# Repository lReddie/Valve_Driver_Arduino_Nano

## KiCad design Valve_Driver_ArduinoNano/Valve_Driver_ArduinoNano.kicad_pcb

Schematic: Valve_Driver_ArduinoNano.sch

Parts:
A1: Arduino_Nano_v3.x; Arduino_Nano
C1, C2, C3, C4, C5, C6, C7, C8, C9, C10, C11, C13, C14, C15, C16, C17, C18, C21, C22, C23, C24, C29, C30, C32: C; C_0603_1608Metric_Pad1.05x0.95mm_HandSolder
C31, C33: C; C_0805_2012Metric_Pad1.15x1.40mm_HandSolder
D1, D2, D3, D4, D5, D6: D_Schottky; D_SOD-123
J1: Barrel_Jack; CUI_PJ-082BH
J2: Conn_01x03_Female; PinHeader_1x03_P2.54mm_Vertical
J3, J4, J5, J6, J8, J9: Conn_01x02; PinHeader_1x02_P2.54mm_Vertical
J7: Conn_01x12; PhoenixContact_MSTBVA_2,5_12-G_1x12_P5.00mm_Vertical
J10: Conn_01x08; PhoenixContact_MSTBV_2,5_8-GF-5,08_1x08_P5.08mm_Vertical_Th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
Q1, Q4, Q7, Q10, Q13, Q17: 2N7002; SOT-23
R1, R2, R3, R4, R5, R6, R7, R8, R9, R10, R11, R13, R15, R16, R17, R19, R20, R31, R34, R38, R40, R42, R44, R45, R46, R50, R58, R60, R65, R67, R68, R69, R70, R77, R79, R80, R81, R82: R; R_0603_1608Metric_Pad1.05x0.95mm_HandSolder
R12, R14, R41, R43, R64, R66: R; R_1206_3216Metric_Pad1.42x1.75mm_HandSolder
SW1, SW2, SW3, SW4, SW5, SW6: SW_Push; SW_SPST_EVQP0
U1: OPA333xxDBV; SOT-23-5
U3, U4, U7, U8, U11, U12: INA186; SOT-23-5_HandSoldering
U14: LM340_SOT223; SOT-223
U15: REF3033; SOT-23

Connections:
+5V: C1.1, C2.1, C3.1, C9.1, C10.1, C17.1, C18.1, C29.1, C32.1, C33.1, R5.2, R6.2, R7.2, R8.2, R10.2, R17.2, U1.5 (V+), U3.3, U4.3, U7.3, U8.3, U11.3, U12.3, U14.3, U15.1 (IN)
+12V: A1.30
/AIR_D_CURR: A1.25, C23.1, R65.1
/AIR_D_Hit: A1.5, R34.2
/AIR_D_On: A1.11, J10.3, R17.1, SW6.1
/AIR_D_RTN: D3.2, J5.2, J7.11, Q7.3 (D)
/AIR_D_VALVE: D3.1, J5.1, J7.12, R58.1, R64.1
/EQ_CURR: A1.21, C8.1, R15.1
/EQ_Hit: A1.9, R70.2
/EQ_On: A1.15, J10.7, R6.1, SW2.1
/EQ_RTN: D5.2, J7.3, J8.2, Q13.3 (D)
/EQ_VALVE: D5.1, J7.4, J8.1, R11.1, R14.1
/FWA_CURR: A1.23, C16.1, R44.1
/FWA_Hit: A1.7, R16.2
/FWA_On: A1.13, J10.5, R8.1, SW4.1
/FWA_RTN: D1.2, J3.2, J7.7, Q1.3 (D)
/FWA_VALVE: D1.1, J3.1, J7.8, R40.1, R43.1
/FWB_CURR: A1.24, C15.1, R42.1
/FWB_Hit: A1.6, R31.2
/FWB_On: A1.12, J10.4, R7.1, SW3.1
/FWB_RTN: D2.2, J4.2, J7.9, Q4.3 (D)
/FWB_VALVE: D2.1, J4.1, J7.10, R38.1, R41.1
/INPUT_POWER: C30.1, C31.1, J1.1, R1.2, R12.2, R14.2, R19.1, R20.1, R41.2, R43.2, R45.1, R46.1, R64.2, R66.2, R68.1, R69.1, U14.1
/OCD_CURR: A1.20, C7.1, R13.1
/OCD_Hit: A1.10, R50.2
/OCD_On: A1.16, J10.8, R5.1, SW1.1
/OCD_RTN: D4.2, J6.2, J7.1, Q10.3 (D)
/OCD_VALVE: D4.1, J6.1, J7.2, R9.1, R12.1
/PUR_CURR: A1.22, C24.1, R67.1
/PUR_Hit: A1.8, R77.2
/PUR_RTN: D6.2, J7.5, J9.2, Q17.3 (D)
/PUR_VALVE: D6.1, J7.6, J9.1, R60.1, R66.1
/Pur_On: A1.14, J10.6, R10.1, SW5.1
/RX: A1.2, J2.1
/TX: A1.1, J2.2
/VALVE_V: A1.19, C4.1, J10.2, R2.2
GND: A1.4, A1.29, C1.2, C2.2, C3.2, C4.2, C7.2, C8.2, C9.2, C10.2, C11.2, C15.2, C16.2, C17.2, C18.2, C23.2, C24.2, C29.2, C30.2, C31.2, C32.2, C33.2, J1.2, J2.3, J10.1, Q1.2 (S), Q4.2 (S), Q7.2 (S), Q10.2 (S), Q13.2 (S), Q17.2 (S), R3.1, SW1.2, SW2.2, SW3.2, SW4.2, SW5.2, SW6.2, U1.2 (V-), U3.1, U4.1, U7.1, U8.1, U11.1, U12.1, U14.2, U14.4, U15.3 (GND)
unnamed: A1.17, R79.1
unnamed: A1.18, R79.2, R80.2, R82.1
unnamed: A1.27, R80.1, R81.1
unnamed: A1.3, A1.28, R81.2
unnamed: C5.1, R9.2, U3.4
unnamed: C5.2, R19.2, U3.5
unnamed: C6.1, R11.2, U4.4
unnamed: C6.2, R20.2, U4.5
unnamed: C11.1, R1.1, R3.2, U1.3 (+)
unnamed: C13.1, R38.2, U7.4
unnamed: C13.2, R45.2, U7.5
unnamed: C14.1, R40.2, U8.4
unnamed: C14.2, R46.2, U8.5
unnamed: C21.1, R58.2, U11.4
unnamed: C21.2, R68.2, U11.5
unnamed: C22.1, R60.2, U12.4
unnamed: C22.2, R69.2, U12.5
unnamed: Q1.1 (G), R16.1
unnamed: Q4.1 (G), R31.1
unnamed: Q7.1 (G), R34.1
unnamed: Q10.1 (G), R50.1
unnamed: Q13.1 (G), R70.1
unnamed: Q17.1 (G), R77.1
unnamed: R2.1, R4.2, U1.1
unnamed: R4.1, U1.4 (-)
unnamed: R13.2, U3.2
unnamed: R15.2, U4.2
unnamed: R42.2, U7.2
unnamed: R44.2, U8.2
unnamed: R65.2, U11.2
unnamed: R67.2, U12.2
unnamed: R82.2, U15.2 (OUT)

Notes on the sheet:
Shield for Arduino Nano

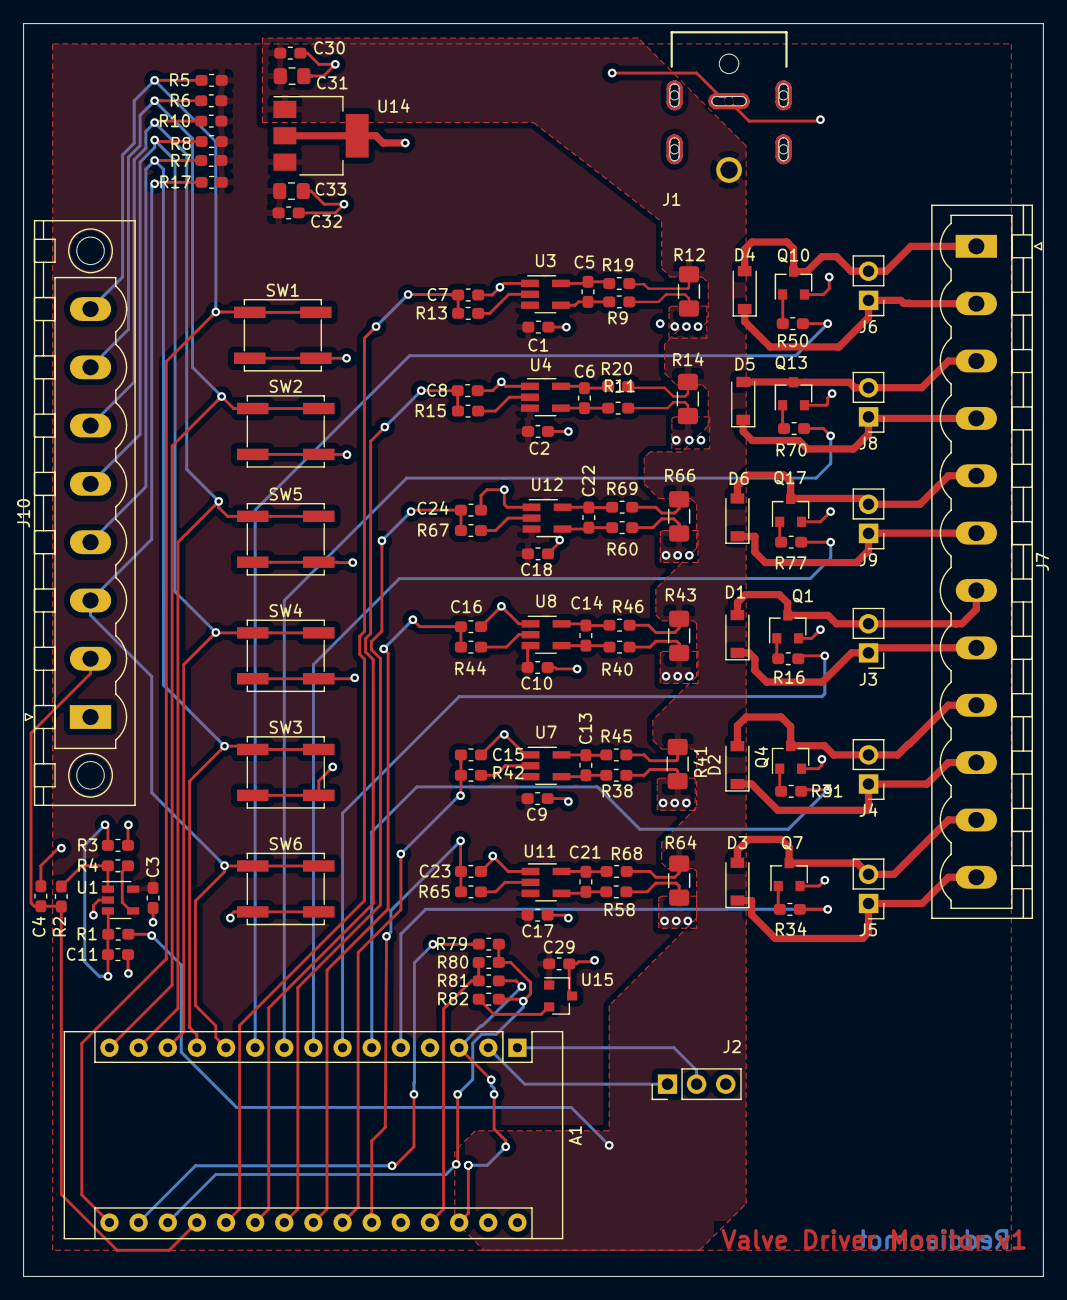
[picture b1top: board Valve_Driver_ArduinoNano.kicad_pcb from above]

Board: 2 copper layers, 88.9 x 109.2 mm, 108 parts (0 on the bottom side), 68 nets.

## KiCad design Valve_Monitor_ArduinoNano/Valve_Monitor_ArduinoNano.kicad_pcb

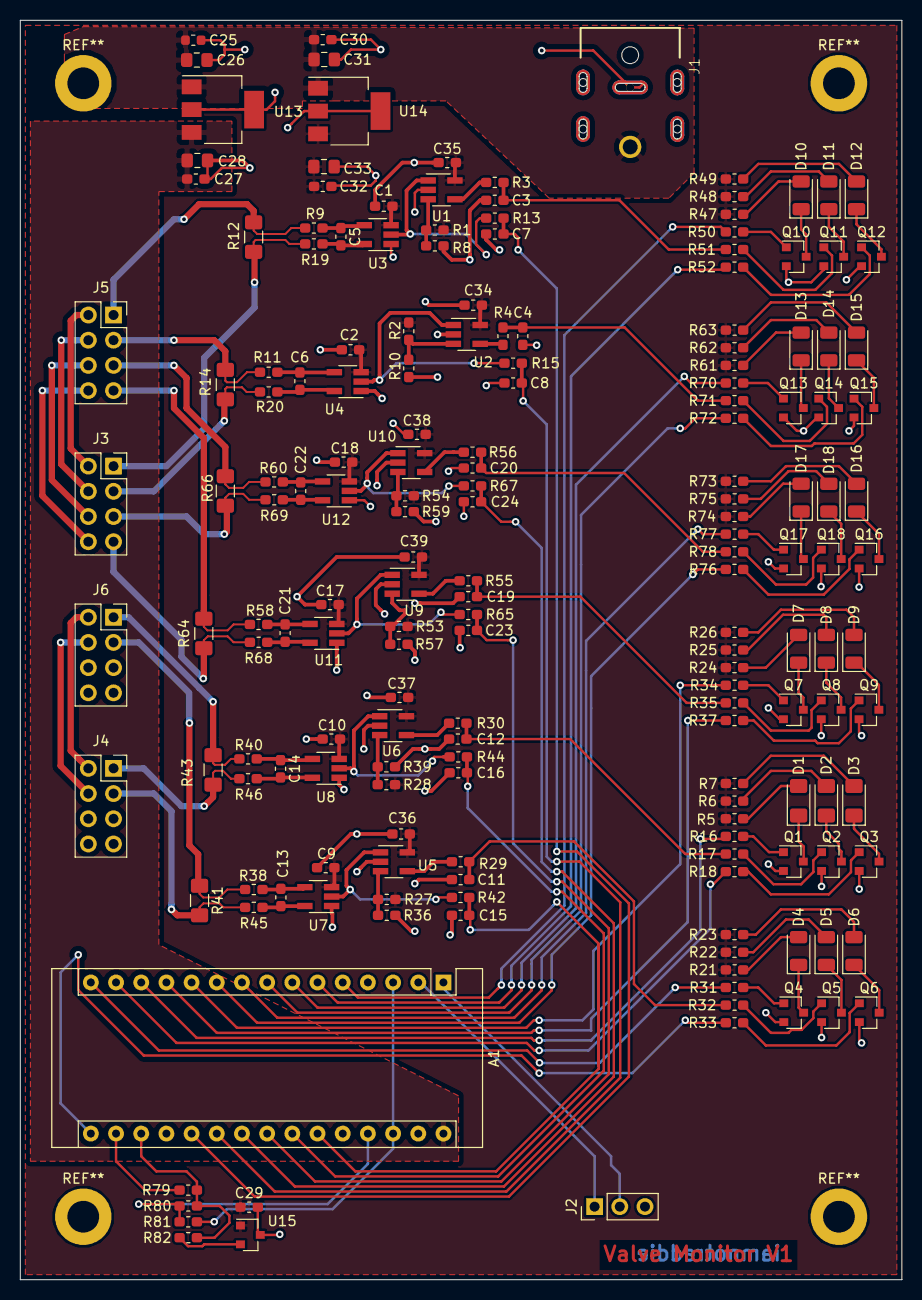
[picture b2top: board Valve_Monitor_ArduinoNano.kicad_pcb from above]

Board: 2 copper layers, 88.9 x 127.0 mm, 179 parts (0 on the bottom side), 137 nets.

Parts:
A1: Arduino_Nano_v3.x; Arduino_Nano
C1, C2, C3, C4, C5, C6, C7, C8, C9, C10, C11, C12, C13, C14, C15, C16, C17, C18, C19, C20, C21, C22, C23, C24, C27, C29, C30, C32, C34, C35, C36, C37, C38, C39: C; C_0603_1608Metric_Pad1.05x0.95mm_HandSolder
C25: C; C_0603_1608Metric
C26, C28, C31, C33: C; C_0805_2012Metric_Pad1.15x1.40mm_HandSolder
D1, D2, D3: LED; LED_1206_3216Metric_Pad1.42x1.75mm_HandSolder
D4, D5, D6, D7, D8, D9, D10, D11, D12, D13, D14, D15, D16, D17, D18: LED; LED_1206_3216Metric
J1: Barrel_Jack; CUI_PJ-082BH
J2: Conn_01x03_Female; PinHeader_1x03_P2.54mm_Vertical
J3, J4, J5, J6: Conn_02x04_Top_Bottom; PinSocket_2x04_P2.54mm_Vertical
Q1, Q2, Q3, Q4, Q5, Q6, Q7, Q8, Q9, Q10, Q11, Q12, Q13, Q14, Q15, Q16, Q17, Q18: 2N7002; SOT-23
R1, R2, R3, R4, R5, R6, R7, R8, R9, R10, R11, R13, R15, R16, R17, R18, R19, R20, R21, R22, R23, R24, R25, R26, R27, R28, R29, R30, R31, R32, R33, R34, R35, R36, R37, R38, R39, R40, R42, R44, R45, R46, R47, R48, R49, R50, R51, R52, R53, R54, R55, R56, R57, R58, R59, R60, R61, R62, R63, R65, R67, R68, R69, R70, R71, R72, R73, R74, R75, R76, R77, R78, R79, R80, R81, R82: R; R_0603_1608Metric_Pad1.05x0.95mm_HandSolder
R12, R14, R41, R43, R64, R66: R; R_1206_3216Metric_Pad1.42x1.75mm_HandSolder
U1, U2, U5, U6, U9, U10: LMV331; SOT-23-5_HandSoldering
U3, U4, U7, U8, U11, U12: INA186; SOT-23-5_HandSoldering
U13, U14: LM340_SOT223; SOT-223
U15: REF3033; SOT-23

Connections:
+5V: C1.1, C2.1, C9.1, C10.1, C17.1, C18.1, C29.1, C32.1, C33.1, C34.1, C35.1, C36.1, C37.1, C38.1, C39.1, R1.1, R2.1, R5.1, R6.1, R7.1, R21.1, R22.1, R23.1, R24.1, R25.1, R26.1, R27.1, R28.1, R47.1, R48.1, R49.1, R53.1, R54.1, R61.1, R62.1, R63.1, R73.1, R74.1, R75.1, U1.5, U2.5, U3.3, U4.3, U5.5, U6.5, U7.3, U8.3, U9.5, U10.5, U11.3, U12.3, U14.3, U15.1
+12V: A1.30, C27.1, C28.1, U13.3
/AIR_D_CURR: A1.23, C23.1, R65.1
/AIR_D_Hit: A1.11, R34.2
/AIR_D_Hold: C19.1, R35.2, R55.1
/AIR_D_PASS: A1.12, R37.2
/AIR_D_PWR: J3.7, R64.2, R68.1
/AIR_D_VALVE: J5.7, R58.1, R64.1
/AIR_D__RTN: J3.8, J5.8
/EQ_CURR: A1.21, C8.1, R15.1
/EQ_Hit: A1.7, R70.2
/EQ_Hold: C4.1, R4.1, R71.2
/EQ_PASS: A1.8, R72.2
/EQ_PWR: J3.3, R14.2, R20.1
/EQ_RTN: J3.4, J5.4
/EQ_VALVE: J5.3, R11.1, R14.1
/FWA_CURR: A1.24, C16.1, R44.1
/FWA_Hit: A1.13, R16.2
/FWA_Hold: C12.1, R17.2, R30.1
/FWA_PASS: A1.14, R18.2
/FWA_PWR: J4.1, R43.2, R46.1
/FWA_RTN: J4.2, J6.2
/FWA_VALVE: J6.1, R40.1, R43.1
/FWB_CURR: A1.25, C15.1, R42.1
/FWB_Hit: A1.15, R31.2
/FWB_Hold: C11.1, R29.1, R32.2
/FWB_PASS: A1.16, R33.2
/FWB_PWR: J4.3, R41.2, R45.1
/FWB_RTN: J4.4, J6.4
/FWB_VALVE: J6.3, R38.1, R41.1
/INPUT_POWER: C25.1, C26.1, C30.1, C31.1, J1.1, U13.1, U14.1
/OCD_CURR: A1.20, C7.1, R13.1
/OCD_Hit: A1.5, R50.2
/OCD_Hold: C3.1, R3.1, R51.2
/OCD_PASS: A1.6, R52.2
/OCD_PWR: J3.1, R12.2, R19.1
/OCD_RTN: J3.2, J5.2
/OCD_VALVE: J5.1, R9.1, R12.1
/PUR_CURR: A1.22, C24.1, R67.1
/PUR_Hit: A1.9, R77.2
/PUR_Hold: C20.1, R56.1, R78.2
/PUR_PASS: A1.10, R76.2
/PUR_PWR: J3.5, R66.2, R69.1
/PUR_RTN: J3.6, J5.6
/PUR_VALVE: J5.5, R60.1, R66.1
/RX: A1.2, J2.1
/TX: A1.1, J2.2
GND: A1.4, A1.29, C1.2, C2.2, C3.2, C4.2, C7.2, C8.2, C9.2, C10.2, C11.2, C12.2, C15.2, C16.2, C17.2, C18.2, C19.2, C20.2, C23.2, C24.2, C25.2, C26.2, C27.2, C28.2, C29.2, C30.2, C31.2, C32.2, C33.2, C34.2, C35.2, C36.2, C37.2, C38.2, C39.2, J1.2, J2.3, Q1.2, Q2.2, Q3.2, Q4.2, Q5.2, Q6.2, Q7.2, Q8.2, Q9.2, Q10.2, Q11.2, Q12.2, Q13.2, Q14.2, Q15.2, Q16.2, Q17.2, Q18.2, R8.2, R10.2, R36.2, R39.2, R57.2, R59.2, U1.2, U2.2, U3.1, U4.1, U5.2, U6.2, U7.1, U8.1, U9.2, U10.2, U11.1, U12.1, U13.2, U13.4, U14.2, U14.4, U15.3
unnamed: A1.17, R79.1
unnamed: A1.18, R79.2, R80.2, R82.1
unnamed: A1.27, R80.1, R81.1
unnamed: A1.3, A1.28, R81.2
unnamed: C5.1, R9.2, U3.4
unnamed: C5.2, R19.2, U3.5
unnamed: C6.1, R11.2, U4.4
unnamed: C6.2, R20.2, U4.5
unnamed: C13.1, R38.2, U7.4
unnamed: C13.2, R45.2, U7.5
unnamed: C14.1, R40.2, U8.4
unnamed: C14.2, R46.2, U8.5
unnamed: C21.1, R58.2, U11.4
unnamed: C21.2, R68.2, U11.5
unnamed: C22.1, R60.2, U12.4
unnamed: C22.2, R69.2, U12.5
unnamed: D1.1, Q1.3
unnamed: D1.2, R5.2
unnamed: D2.1, Q2.3
unnamed: D2.2, R6.2
unnamed: D3.1, Q3.3
unnamed: D3.2, R7.2
unnamed: D4.1, Q4.3
unnamed: D4.2, R21.2
unnamed: D5.1, Q5.3
unnamed: D5.2, R22.2
unnamed: D6.1, Q6.3
unnamed: D6.2, R23.2
unnamed: D7.1, Q7.3
unnamed: D7.2, R24.2
unnamed: D8.1, Q8.3
unnamed: D8.2, R25.2
unnamed: D9.1, Q9.3
unnamed: D9.2, R26.2
unnamed: D10.1, Q10.3
unnamed: D10.2, R47.2
unnamed: D11.1, Q11.3
unnamed: D11.2, R48.2
unnamed: D12.1, Q12.3
unnamed: D12.2, R49.2
unnamed: D13.1, Q13.3
unnamed: D13.2, R61.2
unnamed: D14.1, Q14.3
unnamed: D14.2, R62.2
unnamed: D15.1, Q15.3
unnamed: D15.2, R63.2
unnamed: D16.1, Q16.3
unnamed: D16.2, R73.2
unnamed: D17.1, Q17.3
unnamed: D17.2, R74.2
unnamed: D18.1, Q18.3
unnamed: D18.2, R75.2
unnamed: Q1.1, R16.1
unnamed: Q2.1, R17.1
unnamed: Q3.1, R18.1
unnamed: Q4.1, R31.1
unnamed: Q5.1, R32.1
unnamed: Q6.1, R33.1
unnamed: Q7.1, R34.1
unnamed: Q8.1, R35.1
unnamed: Q9.1, R37.1
unnamed: Q10.1, R50.1
unnamed: Q11.1, R51.1
unnamed: Q12.1, R52.1
unnamed: Q13.1, R70.1
unnamed: Q14.1, R71.1
unnamed: Q15.1, R72.1
unnamed: Q16.1, R76.1
unnamed: Q17.1, R77.1
unnamed: Q18.1, R78.1
unnamed: R1.2, R8.1, U1.3
unnamed: R3.2, U1.4
unnamed: R4.2, U2.4
unnamed: R2.2, R10.1, U2.3
unnamed: R13.2, U1.1, U3.2
unnamed: R15.2, U2.1, U4.2
unnamed: R27.2, R36.1, U5.3
unnamed: R28.2, R39.1, U6.3
unnamed: R29.2, U5.4
unnamed: R30.2, U6.4
unnamed: R42.2, U5.1, U7.2
unnamed: R44.2, U6.1, U8.2
unnamed: R53.2, R57.1, U9.3
unnamed: R54.2, R59.1, U10.3
unnamed: R55.2, U9.4
unnamed: R56.2, U10.4
unnamed: R65.2, U9.1, U11.2
unnamed: R67.2, U10.1, U12.2
unnamed: R82.2, U15.2
